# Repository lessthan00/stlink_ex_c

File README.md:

# stlink_ex_c

这是ST-LINK的转接板

stlink_ex_c: pin5 改为 pin7 , 改为VDD SWDIO SWCLK GND NRST JTDI JTDO

stlink_ex_b: 修改了板子的形状, 2x7 2x5 改为简易牛角接口, 丝印改到正确的位置

stlink_ex_a: JTGA 和SWD1.27mm间距和2.54mm间距

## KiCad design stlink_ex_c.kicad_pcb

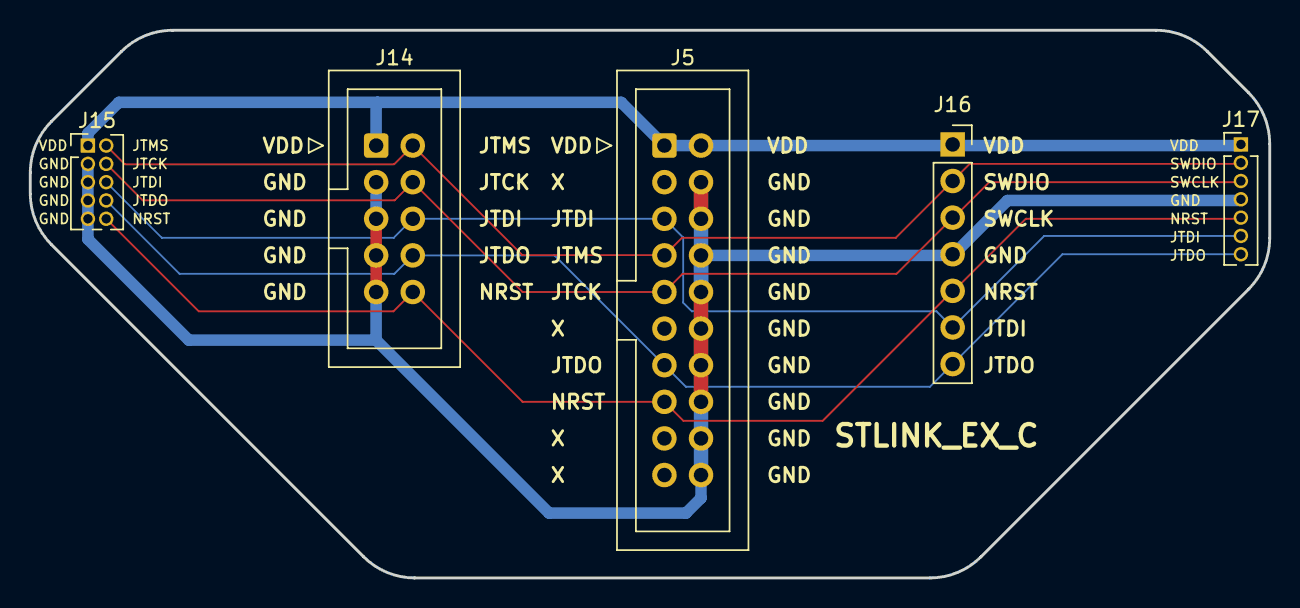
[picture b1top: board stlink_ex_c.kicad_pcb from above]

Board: 2 copper layers, 86.0 x 38.0 mm, 5 parts (0 on the bottom side), 7 nets.

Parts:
J5: Conn_02x10_Odd_Even; IDC-Header_2x10_P2.54mm_Vertical
J14: Conn_02x05_Odd_Even; IDC-Header_2x05_P2.54mm_Vertical
J15: Conn_02x05_Odd_Even; PinHeader_2x05_P1.27mm_Vertical
J16: Conn_01x07; PinSocket_1x07_P2.54mm_Vertical
J17: Conn_01x07; PinHeader_1x07_P1.27mm_Vertical

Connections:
/GND: J5.4, J5.6, J5.8, J5.10, J5.12, J5.14, J5.16, J5.18, J5.20, J14.3, J14.5, J14.7, J14.9, J15.3, J15.5, J15.7, J15.9, J16.4, J17.4
/JTCK: J5.9, J14.4, J15.4, J16.3, J17.3
/JTDI: J5.5, J14.6, J15.6, J16.6, J17.6
/JTDO: J5.13, J14.8, J15.8, J16.7, J17.7
/JTMS: J5.7, J14.2, J15.2, J16.2, J17.2
/MCU VDD: J5.1, J5.2, J14.1, J15.1, J16.1, J17.1
/NRST: J5.15, J14.10, J15.10, J16.5, J17.5
